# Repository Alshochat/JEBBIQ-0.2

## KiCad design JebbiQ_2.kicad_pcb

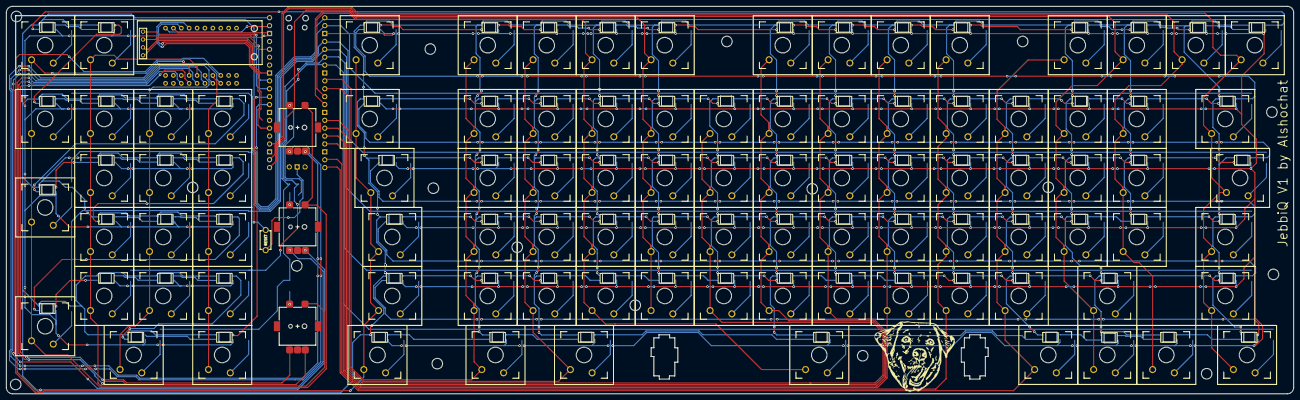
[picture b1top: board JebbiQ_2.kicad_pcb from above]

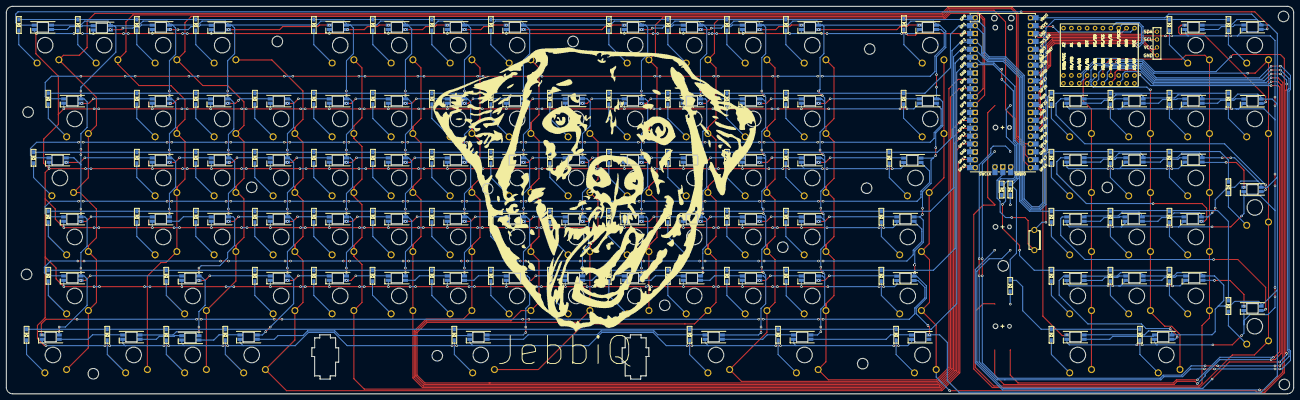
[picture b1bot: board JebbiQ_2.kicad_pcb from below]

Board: 2 copper layers, 414.5 x 124.8 mm, 295 parts (97 on the bottom side), 232 nets.

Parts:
D1, D2, D3, D4, D5, D6, D7, D8, D9, D10, D11, D12, D13, D14, D15, D16, D17, D18, D19, D20, D21, D22, D23, D24, D25, D26, D27, D28, D29, D30, D31, D32, D33, D34, D35, D36, D37, D38, D39, D40, D41, D42, D43, D44, D45, D46, D47, D48, D49, D50, D51, D52, D53, D54, D55, D56, D57, D58, D59, D60, D62, D63, D64, D65, D66, D68, D69, D70, D71, D72, D74, D75, D76, D77, D78, D80, D81, D82, D83, D84, D85, D86, D87, D88, D89, D90, D91, D92, D93, D94, D95, D97, D98, D99, D100, D101, D102, D103: SofleKeyboard-rescue_D-Lily58-cache-Lily58_Pro-re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; crkbd-diode
J1: SofleKeyboard-rescue_OLED-Lily58-cache-Lily58_Pro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; OLED_4Pin_1306
LED1, LED2, LED3, LED4, LED5, LED6, LED7, LED8, LED9, LED10, LED11, LED12, LED13, LED14, LED15, LED16, LED17, LED18, LED19, LED20, LED21, LED22, LED23, LED24, LED25, LED26, LED27, LED28, LED29, LED30, LED31, LED32, LED33, LED34, LED35, LED36, LED37, LED38, LED39, LED40, LED41, LED42, LED43, LED44, LED45, LED46, LED47, LED48, LED49, LED50, LED51, LED52, LED53, LED54, LED55, LED56, LED57, LED58, LED59, LED60, LED61, LED62, LED63, LED64, LED65, LED66, LED67, LED68, LED69, LED70, LED71, LED72, LED73, LED74, LED75, LED76, LED77, LED78, LED79, LED80, LED81, LED82, LED83, LED84, LED85, LED86, LED87, LED88, LED89, LED90, LED91, LED92, LED93, LED94, LED95: YS-SK6812MINI-E
MCP1: MCP23017 module
RSW1: SofleKeyboard-rescue_SW_RST-Lily58-cache-Lily58_P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; TACT_SWITCH_TVBP06
SW1, SW2, SW3, SW4, SW5, SW6, SW7, SW8, SW9, SW10, SW11, SW12, SW13, SW14, SW15, SW16, SW17, SW18, SW19, SW20, SW21, SW22, SW23, SW24, SW25, SW26, SW27, SW28, SW29, SW30, SW31, SW32, SW33, SW34, SW35, SW36, SW37, SW38, SW39, SW40, SW41, SW42, SW43, SW44, SW45, SW46, SW47, SW48, SW51, SW52, SW53, SW54, SW56, SW57, SW58, SW59, SW60, SW62, SW63, SW64, SW65, SW66, SW68, SW69, SW70, SW71, SW72, SW74, SW75, SW76, SW77, SW78, SW80, SW81, SW82, SW83, SW84, SW85, SW86, SW87, SW88, SW89, SW90, SW91, SW92, SW93, SW94, SW95, SW97, SW98, SW99, SW100, SW101, SW102, SW103: SW_PUSH-Lily58-cache-Lily58_Pro-rescue; LOW_profile_switch
SW49, SW50, SW104: SofleKeyboard-rescue_Rotary_Encoder_Switch-Device; RotaryEncoder_Alps_EC11E-Switch_Vertical_H20mm-keebio_modif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
U49: Pico; RPi_Pico_SMD_TH

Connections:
COL1: MCP1.17 (B4), SW1.1, SW3.1, SW7.1, SW14.1, SW49.S1, SW104.S1
COL2: MCP1.16 (B3), SW2.1, SW4.1, SW8.1, SW11.1, SW15.1, SW50.S1
COL3: MCP1.15 (B2), SW5.1, SW9.1, SW12.1, SW16.1, SW18.1
COL4: MCP1.14 (B1), SW6.1, SW10.1, SW13.1, SW17.1, SW19.1
COL5: MCP1.13 (B0), SW20.1, SW21.1, SW22.1, SW23.1, SW24.1, SW25.1
COL6: SW26.1, SW27.1, SW28.1, SW29.1, SW30.1, SW31.1, U49.9 (GPIO6)
COL7: SW32.1, SW33.1, SW34.1, SW35.1, SW36.1, SW37.1, U49.10 (GPIO7)
COL8: SW38.1, SW39.1, SW40.1, SW41.1, SW42.1, SW43.1, U49.11 (GPIO8)
COL9: SW44.1, SW45.1, SW46.1, SW47.1, SW48.1, U49.12 (GPIO9)
COL10: SW51.1, SW52.1, SW53.1, SW54.1, U49.14 (GPIO10)
COL11: SW56.1, SW57.1, SW58.1, SW59.1, SW60.1, U49.15 (GPIO11)
COL12: SW62.1, SW63.1, SW64.1, SW65.1, SW66.1, U49.16 (GPIO12)
COL13: SW68.1, SW69.1, SW70.1, SW71.1, SW72.1, U49.17 (GPIO13)
COL14: SW74.1, SW75.1, SW76.1, SW77.1, SW78.1, U49.19 (GPIO14)
COL15: SW80.1, SW81.1, SW82.1, SW83.1, SW84.1, SW85.1, U49.20 (GPIO15)
COL16: SW86.1, SW87.1, SW88.1, SW89.1, SW90.1, SW91.1, U49.21 (GPIO16)
COL17: SW92.1, SW93.1, SW94.1, SW95.1, SW97.1, U49.22 (GPIO17)
COL18: SW98.1, SW99.1, SW100.1, SW101.1, SW102.1, SW103.1, U49.24 (GPIO18)
ENC1 A: MCP1.28 (A0), SW104.A
ENC1 B: MCP1.27 (A1), SW104.B
ENC2 A: MCP1.26 (A2), SW49.A
ENC2 B: MCP1.25 (A3), SW49.B
ENC3 A: MCP1.24 (A4), SW50.A
ENC3 B: MCP1.23 (A5), SW50.B
GND: J1.4, LED1.3 (VSS), LED2.3 (VSS), LED3.3 (VSS), LED5.3 (VSS), LED6.3 (VSS), LED7.3 (VSS), LED8.3 (VSS), LED9.3 (VSS), LED10.3 (VSS), LED11.3 (VSS), LED12.3 (VSS), LED13.3 (VSS), LED14.3 (VSS), LED15.3 (VSS), LED16.3 (VSS), LED17.3 (VSS), LED18.3 (VSS), LED19.3 (VSS), LED20.3 (VSS), LED21.3 (VSS), LED22.3 (VSS), LED23.3 (VSS), LED24.3 (VSS), LED25.3 (VSS), LED26.3 (VSS), LED27.3 (VSS), LED28.3 (VSS), LED29.3 (VSS), LED30.3 (VSS), LED31.3 (VSS), LED32.3 (VSS), LED33.3 (VSS), LED34.3 (VSS), LED35.3 (VSS), LED36.3 (VSS), LED37.3 (VSS), LED38.3 (VSS), LED39.3 (VSS), LED40.3 (VSS), LED41.3 (VSS), LED42.3 (VSS), LED43.3 (VSS), LED44.3 (VSS), LED45.3 (VSS), LED46.3 (VSS), LED47.3 (VSS), LED48.3 (VSS), LED49.3 (VSS), LED50.3 (VSS), LED51.3 (VSS), LED52.3 (VSS), LED53.3 (VSS), LED54.3 (VSS), LED55.3 (VSS), LED56.3 (VSS), LED57.3 (VSS), LED58.3 (VSS), LED59.3 (VSS), LED60.3 (VSS), LED61.3 (VSS), LED62.3 (VSS), LED63.3 (VSS), LED64.3 (VSS), LED65.3 (VSS), LED66.3 (VSS), LED67.3 (VSS), LED68.3 (VSS), LED69.3 (VSS), LED70.3 (VSS), LED71.3 (VSS), LED72.3 (VSS), LED73.3 (VSS), LED74.3 (VSS), LED75.3 (VSS), LED76.3 (VSS), LED77.3 (VSS), LED78.3 (VSS), LED79.3 (VSS), LED80.3 (VSS), LED81.3 (VSS), LED82.3 (VSS), LED83.3 (VSS), LED84.3 (VSS), LED85.3 (VSS), LED86.3 (VSS), LED87.3 (VSS), LED88.3 (VSS), LED89.3 (VSS), LED90.3 (VSS), LED91.3 (VSS), LED92.3 (VSS), LED93.3 (VSS), LED94.3 (VSS), LED95.3 (VSS), MCP1.9 (GND), MCP1.30 (GND), RSW1.1, U49.3 (GND), U49.8 (GND), U49.13 (GND), U49.18 (GND), U49.23 (GND), U49.28 (GND), U49.33 (AGND), U49.38 (GND), U49.42 (GND)
LED CTRL: LED19.4 (DIN), U49.29 (GPIO22)
LED PWR: LED1.1 (VDD), LED2.1 (VDD), LED3.1 (VDD), LED4.1 (VDD), LED5.1 (VDD), LED6.1 (VDD), LED7.1 (VDD), LED8.1 (VDD), LED9.1 (VDD), LED10.1 (VDD), LED11.1 (VDD), LED12.1 (VDD), LED13.1 (VDD), LED14.1 (VDD), LED15.1 (VDD), LED16.1 (VDD), LED17.1 (VDD), LED18.1 (VDD), LED19.1 (VDD), LED20.1 (VDD), LED21.1 (VDD), LED22.1 (VDD), LED23.1 (VDD), LED24.1 (VDD), LED25.1 (VDD), LED26.1 (VDD), LED27.1 (VDD), LED28.1 (VDD), LED29.1 (VDD), LED30.1 (VDD), LED31.1 (VDD), LED32.1 (VDD), LED33.1 (VDD), LED34.1 (VDD), LED35.1 (VDD), LED36.1 (VDD), LED37.1 (VDD), LED38.1 (VDD), LED39.1 (VDD), LED40.1 (VDD), LED41.1 (VDD), LED42.1 (VDD), LED43.1 (VDD), LED44.1 (VDD), LED45.1 (VDD), LED46.1 (VDD), LED47.1 (VDD), LED48.1 (VDD), LED49.1 (VDD), LED50.1 (VDD), LED51.1 (VDD), LED52.1 (VDD), LED53.1 (VDD), LED54.1 (VDD), LED55.1 (VDD), LED56.1 (VDD), LED57.1 (VDD), LED58.1 (VDD), LED59.1 (VDD), LED60.1 (VDD), LED61.1 (VDD), LED62.1 (VDD), LED63.1 (VDD), LED64.1 (VDD), LED65.1 (VDD), LED66.1 (VDD), LED67.1 (VDD), LED68.1 (VDD), LED69.1 (VDD), LED70.1 (VDD), LED71.1 (VDD), LED72.1 (VDD), LED73.1 (VDD), LED74.1 (VDD), LED75.1 (VDD), LED76.1 (VDD), LED77.1 (VDD), LED78.1 (VDD), LED79.1 (VDD), LED80.1 (VDD), LED81.1 (VDD), LED82.1 (VDD), LED83.1 (VDD), LED84.1 (VDD), LED85.1 (VDD), LED86.1 (VDD), LED87.1 (VDD), LED88.1 (VDD), LED89.1 (VDD), LED90.1 (VDD), LED91.1 (VDD), LED92.1 (VDD), LED93.1 (VDD), LED94.1 (VDD), LED95.1 (VDD), U49.40 (VBUS)
MCP PWR: MCP1.10 (VCC), MCP1.11 (VCC), U49.39 (VSYS)
unnamed: D1.2 (A), SW1.2
unnamed: D2.2 (A), SW2.2
unnamed: D3.2 (A), SW3.2
unnamed: D4.2 (A), SW4.2
unnamed: D5.2 (A), SW5.2
unnamed: D6.2 (A), SW6.2
unnamed: D7.2 (A), SW7.2
unnamed: D8.2 (A), SW8.2
unnamed: D9.2 (A), SW9.2
unnamed: D10.2 (A), SW10.2
unnamed: D11.2 (A), SW11.2
unnamed: D12.2 (A), SW12.2
unnamed: D13.2 (A), SW13.2
unnamed: D14.2 (A), SW14.2
unnamed: D15.2 (A), SW15.2
unnamed: D16.2 (A), SW16.2
unnamed: D17.2 (A), SW17.2
unnamed: D18.2 (A), SW18.2
unnamed: D19.2 (A), SW19.2
unnamed: D20.2 (A), SW20.2
unnamed: D21.2 (A), SW21.2
unnamed: D22.2 (A), SW22.2
unnamed: D23.2 (A), SW23.2
unnamed: D24.2 (A), SW24.2
unnamed: D25.2 (A), SW25.2
unnamed: D26.2 (A), SW26.2
unnamed: D27.2 (A), SW27.2
unnamed: D28.2 (A), SW28.2
unnamed: D29.2 (A), SW29.2
unnamed: D30.2 (A), SW30.2
unnamed: D31.2 (A), SW31.2
unnamed: D32.2 (A), SW32.2
unnamed: D33.2 (A), SW33.2
unnamed: D34.2 (A), SW34.2
unnamed: D35.2 (A), SW35.2
unnamed: D36.2 (A), SW36.2
unnamed: D37.2 (A), SW37.2
unnamed: D38.2 (A), SW38.2
unnamed: D39.2 (A), SW39.2
unnamed: D40.2 (A), SW40.2
unnamed: D41.2 (A), SW41.2
unnamed: D42.2 (A), SW42.2
unnamed: D43.2 (A), SW43.2
unnamed: D44.2 (A), SW44.2
unnamed: D45.2 (A), SW45.2
unnamed: D46.2 (A), SW46.2
unnamed: D47.2 (A), SW47.2
unnamed: D48.2 (A), SW48.2
unnamed: D49.2 (A), SW104.S2
unnamed: D50.2 (A), SW49.S2
unnamed: D51.2 (A), SW51.2
unnamed: D52.2 (A), SW52.2
unnamed: D53.2 (A), SW53.2
unnamed: D54.2 (A), SW54.2
unnamed: D55.2 (A), SW50.S2
unnamed: D56.2 (A), SW56.2
unnamed: D57.2 (A), SW57.2
unnamed: D58.2 (A), SW58.2
unnamed: D59.2 (A), SW59.2
unnamed: D60.2 (A), SW60.2
unnamed: D62.2 (A), SW62.2
unnamed: D63.2 (A), SW63.2
unnamed: D64.2 (A), SW64.2
unnamed: D65.2 (A), SW65.2
unnamed: D66.2 (A), SW66.2
unnamed: D68.2 (A), SW68.2
unnamed: D69.2 (A), SW69.2
unnamed: D70.2 (A), SW70.2
unnamed: D71.2 (A), SW71.2
unnamed: D72.2 (A), SW72.2
unnamed: D74.2 (A), SW74.2
unnamed: D75.2 (A), SW75.2
unnamed: D76.2 (A), SW76.2
unnamed: D77.2 (A), SW77.2
unnamed: D78.2 (A), SW78.2
unnamed: D80.2 (A), SW80.2
unnamed: D81.2 (A), SW81.2
unnamed: D82.2 (A), SW82.2
unnamed: D83.2 (A), SW83.2
unnamed: D84.2 (A), SW84.2
unnamed: D85.2 (A), SW85.2
unnamed: D86.2 (A), SW86.2
unnamed: D87.2 (A), SW87.2
unnamed: D88.2 (A), SW88.2
unnamed: D89.2 (A), SW89.2
unnamed: D90.2 (A), SW90.2
unnamed: D91.2 (A), SW91.2
unnamed: D92.2 (A), SW92.2
unnamed: D93.2 (A), SW93.2
unnamed: D94.2 (A), SW94.2
unnamed: D95.2 (A), SW95.2
unnamed: D97.2 (A), SW97.2
unnamed: D98.2 (A), SW98.2
unnamed: D99.2 (A), SW99.2
unnamed: D100.2 (A), SW100.2
unnamed: D101.2 (A), SW101.2
unnamed: D102.2 (A), SW102.2
unnamed: D103.2 (A), SW103.2
unnamed: LED1.4 (DIN), LED5.2 (DOUT)
unnamed: LED1.2 (DOUT), LED90.4 (DIN)
unnamed: LED2.4 (DIN), LED6.2 (DOUT)
unnamed: LED2.2 (DOUT), LED5.4 (DIN)
unnamed: LED3.4 (DIN), LED7.2 (DOUT)
unnamed: LED4.4 (DIN), LED9.2 (DOUT)
unnamed: LED10.4 (DIN), LED15.2 (DOUT)
unnamed: LED6.4 (DIN), LED10.2 (DOUT)
unnamed: LED11.4 (DIN), LED16.2 (DOUT)
unnamed: LED7.4 (DIN), LED11.2 (DOUT)
unnamed: LED8.2 (DOUT), LED12.4 (DIN)
unnamed: LED12.2 (DOUT), LED16.4 (DIN)
unnamed: LED13.4 (DIN), LED18.2 (DOUT)
unnamed: LED9.4 (DIN), LED13.2 (DOUT)
unnamed: LED14.4 (DIN), LED19.2 (DOUT)
unnamed: LED14.2 (DOUT), LED18.4 (DIN)
unnamed: LED3.2 (DOUT), LED15.4 (DIN)
unnamed: LED4.2 (DOUT), LED17.4 (DIN)
unnamed: LED8.4 (DIN), LED17.2 (DOUT)
unnamed: LED20.4 (DIN), LED26.2 (DOUT)
unnamed: LED20.2 (DOUT), LED91.4 (DIN)
unnamed: LED21.4 (DIN), LED27.2 (DOUT)
unnamed: LED21.2 (DOUT), LED92.4 (DIN)
unnamed: LED22.4 (DIN), LED28.2 (DOUT)
unnamed: LED22.2 (DOUT), LED93.4 (DIN)
unnamed: LED23.4 (DIN), LED29.2 (DOUT)
unnamed: LED23.2 (DOUT), LED94.4 (DIN)
unnamed: LED24.4 (DIN), LED30.2 (DOUT)
unnamed: LED24.2 (DOUT), LED95.4 (DIN)
unnamed: LED25.4 (DIN), LED31.2 (DOUT)
unnamed: LED26.4 (DIN), LED32.2 (DOUT)
unnamed: LED27.4 (DIN), LED33.2 (DOUT)
unnamed: LED28.4 (DIN), LED34.2 (DOUT)
unnamed: LED29.4 (DIN), LED35.2 (DOUT)
unnamed: LED30.4 (DIN), LED36.2 (DOUT)
unnamed: LED31.4 (DIN), LED37.2 (DOUT)
unnamed: LED32.4 (DIN), LED38.2 (DOUT)
unnamed: LED33.4 (DIN), LED39.2 (DOUT)
unnamed: LED34.4 (DIN), LED40.2 (DOUT)
unnamed: LED35.4 (DIN), LED41.2 (DOUT)
unnamed: LED36.4 (DIN), LED42.2 (DOUT)
unnamed: LED37.4 (DIN), LED43.2 (DOUT)
unnamed: LED38.4 (DIN), LED44.2 (DOUT)
unnamed: LED39.4 (DIN), LED45.2 (DOUT)
unnamed: LED40.4 (DIN), LED46.2 (DOUT)
unnamed: LED41.4 (DIN), LED47.2 (DOUT)
unnamed: LED42.4 (DIN), LED48.2 (DOUT)
unnamed: LED43.4 (DIN), LED78.2 (DOUT)
unnamed: LED44.4 (DIN), LED53.2 (DOUT)
unnamed: LED45.4 (DIN), LED49.2 (DOUT)
unnamed: LED46.4 (DIN), LED50.2 (DOUT)
unnamed: LED47.4 (DIN), LED51.2 (DOUT)
unnamed: LED48.4 (DIN), LED52.2 (DOUT)
unnamed: LED49.4 (DIN), LED54.2 (DOUT)
unnamed: LED50.4 (DIN), LED55.2 (DOUT)
unnamed: LED51.4 (DIN), LED56.4 (DIN)
unnamed: LED52.4 (DIN), LED57.2 (DOUT)
unnamed: LED53.4 (DIN), LED58.2 (DOUT)
unnamed: LED54.4 (DIN), LED59.2 (DOUT)
unnamed: LED55.4 (DIN), LED60.2 (DOUT)
unnamed: LED56.2 (DOUT), LED61.2 (DOUT)
unnamed: LED57.4 (DIN), LED62.2 (DOUT)
unnamed: LED58.4 (DIN), LED63.2 (DOUT)
unnamed: LED59.4 (DIN), LED64.2 (DOUT)
unnamed: LED60.4 (DIN), LED65.2 (DOUT)
unnamed: LED61.4 (DIN), LED66.2 (DOUT)
unnamed: LED62.4 (DIN), LED67.2 (DOUT)
unnamed: LED63.4 (DIN), LED68.2 (DOUT)
unnamed: LED64.4 (DIN), LED69.2 (DOUT)
unnamed: LED65.4 (DIN), LED70.2 (DOUT)
unnamed: LED66.4 (DIN), LED71.2 (DOUT)
unnamed: LED67.4 (DIN), LED72.2 (DOUT)
unnamed: LED68.4 (DIN), LED73.2 (DOUT)
unnamed: LED69.4 (DIN), LED74.2 (DOUT)
unnamed: LED70.4 (DIN), LED75.2 (DOUT)
unnamed: LED71.4 (DIN), LED76.2 (DOUT)
unnamed: LED72.4 (DIN), LED77.2 (DOUT)
unnamed: LED73.4 (DIN), LED79.2 (DOUT)
unnamed: LED74.4 (DIN), LED80.2 (DOUT)
unnamed: LED75.4 (DIN), LED81.2 (DOUT)
unnamed: LED76.4 (DIN), LED82.2 (DOUT)
unnamed: LED77.4 (DIN), LED83.2 (DOUT)
unnamed: LED78.4 (DIN), LED84.2 (DOUT)
unnamed: LED79.4 (DIN), LED85.2 (DOUT)
unnamed: LED80.4 (DIN), LED86.2 (DOUT)
unnamed: LED81.4 (DIN), LED87.2 (DOUT)
unnamed: LED82.4 (DIN), LED88.2 (DOUT)
unnamed: LED83.4 (DIN), LED94.2 (DOUT)
unnamed: LED84.4 (DIN), LED89.2 (DOUT)
unnamed: LED85.4 (DIN), LED90.2 (DOUT)
unnamed: LED86.4 (DIN), LED91.2 (DOUT)
unnamed: LED87.4 (DIN), LED92.2 (DOUT)
unnamed: LED88.4 (DIN), LED93.2 (DOUT)
unnamed: LED89.4 (DIN), LED95.2 (DOUT)
OLED PWR: J1.3, U49.36 (3V3)
OLED SCL: J1.2, U49.32 (GPIO27_ADC1)
OLED SDA: J1.1, U49.31 (GPIO26_ADC0)
ROW1: D1.1 (K), D2.1 (K), D20.1 (K), D26.1 (K), D32.1 (K), D38.1 (K), D44.1 (K), D56.1 (K), D62.1 (K), D68.1 (K), D74.1 (K), D80.1 (K), D86.1 (K), D92.1 (K), D98.1 (K), U49.1 (GPIO0)
ROW2: D3.1 (K), D4.1 (K), D5.1 (K), D6.1 (K), D21.1 (K), D27.1 (K), D33.1 (K), D39.1 (K), D45.1 (K), D51.1 (K), D57.1 (K), D63.1 (K), D69.1 (K), D75.1 (K), D81.1 (K), D87.1 (K), D93.1 (K), D99.1 (K), U49.2 (GPIO1)
ROW3: D7.1 (K), D8.1 (K), D9.1 (K), D10.1 (K), D22.1 (K), D28.1 (K), D34.1 (K), D40.1 (K), D46.1 (K), D52.1 (K), D58.1 (K), D64.1 (K), D70.1 (K), D76.1 (K), D82.1 (K), D88.1 (K), D94.1 (K), D100.1 (K), U49.4 (GPIO2)
ROW4: D11.1 (K), D12.1 (K), D13.1 (K), D14.1 (K), D23.1 (K), D29.1 (K), D35.1 (K), D41.1 (K), D47.1 (K), D53.1 (K), D59.1 (K), D65.1 (K), D71.1 (K), D77.1 (K), D83.1 (K), D89.1 (K), D95.1 (K), D101.1 (K), U49.5 (GPIO3)
ROW5: D15.1 (K), D16.1 (K), D17.1 (K), D24.1 (K), D30.1 (K), D36.1 (K), D42.1 (K), D48.1 (K), D49.1 (K), D54.1 (K), D60.1 (K), D66.1 (K), D72.1 (K), D78.1 (K), D84.1 (K), D90.1 (K), D102.1 (K), U49.6 (GPIO4)
ROW6: D18.1 (K), D19.1 (K), D25.1 (K), D31.1 (K), D37.1 (K), D43.1 (K), D50.1 (K), D55.1 (K), D85.1 (K), D91.1 (K), D97.1 (K), D103.1 (K), U49.7 (GPIO5)
RST: RSW1.2, U49.30 (RUN)
SCL: MCP1.8 (SCL/SCK), U49.27 (GPIO21)
SDA: MCP1.7 (SDA/SI), U49.26 (GPIO20)
